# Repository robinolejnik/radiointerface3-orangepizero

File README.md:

# radiointerface3-orangepizero
Interface with audio, ptt, squelch and uart lines to connect 3 radios to an OrangePi Zero

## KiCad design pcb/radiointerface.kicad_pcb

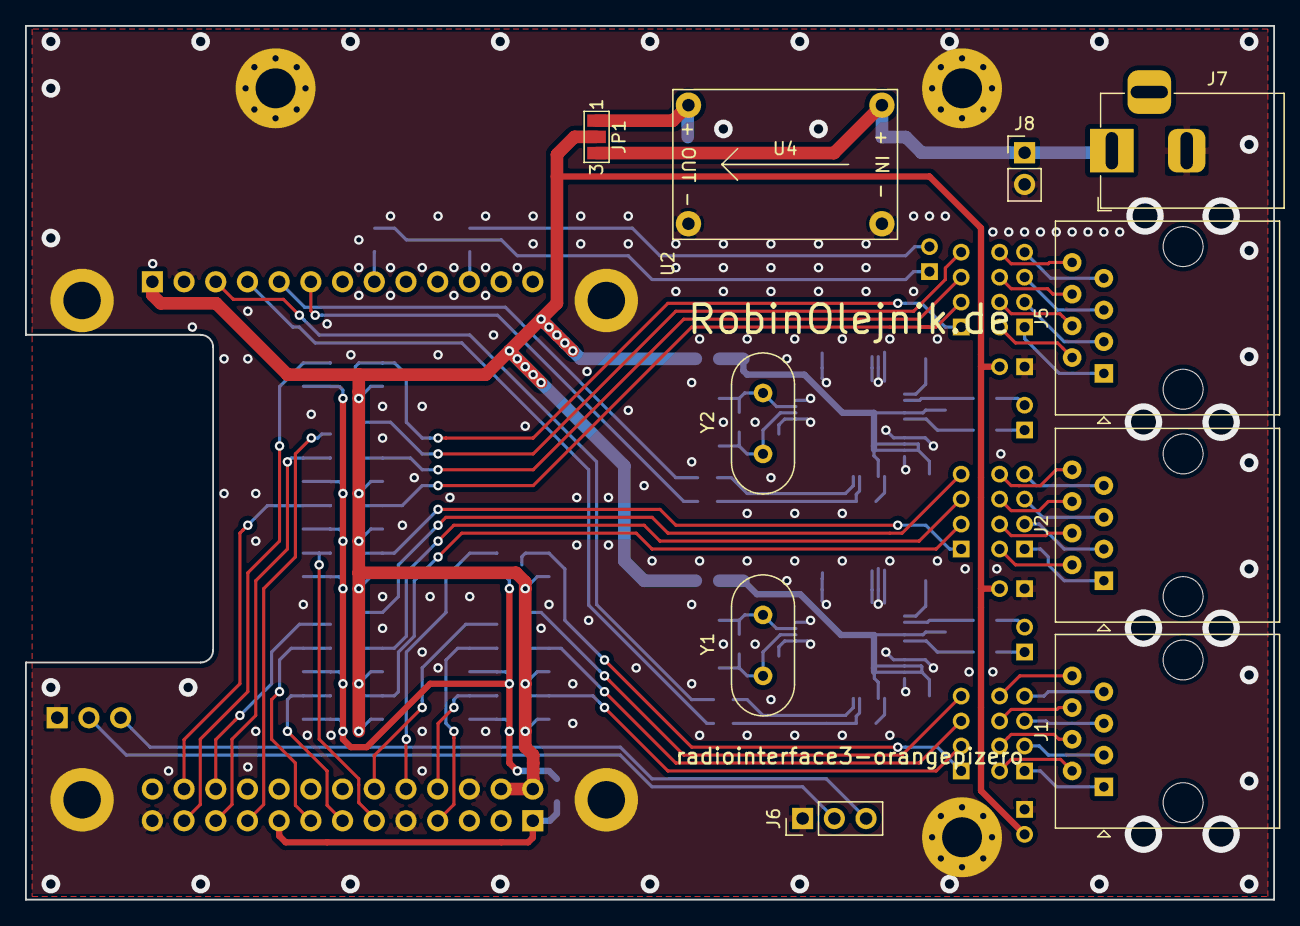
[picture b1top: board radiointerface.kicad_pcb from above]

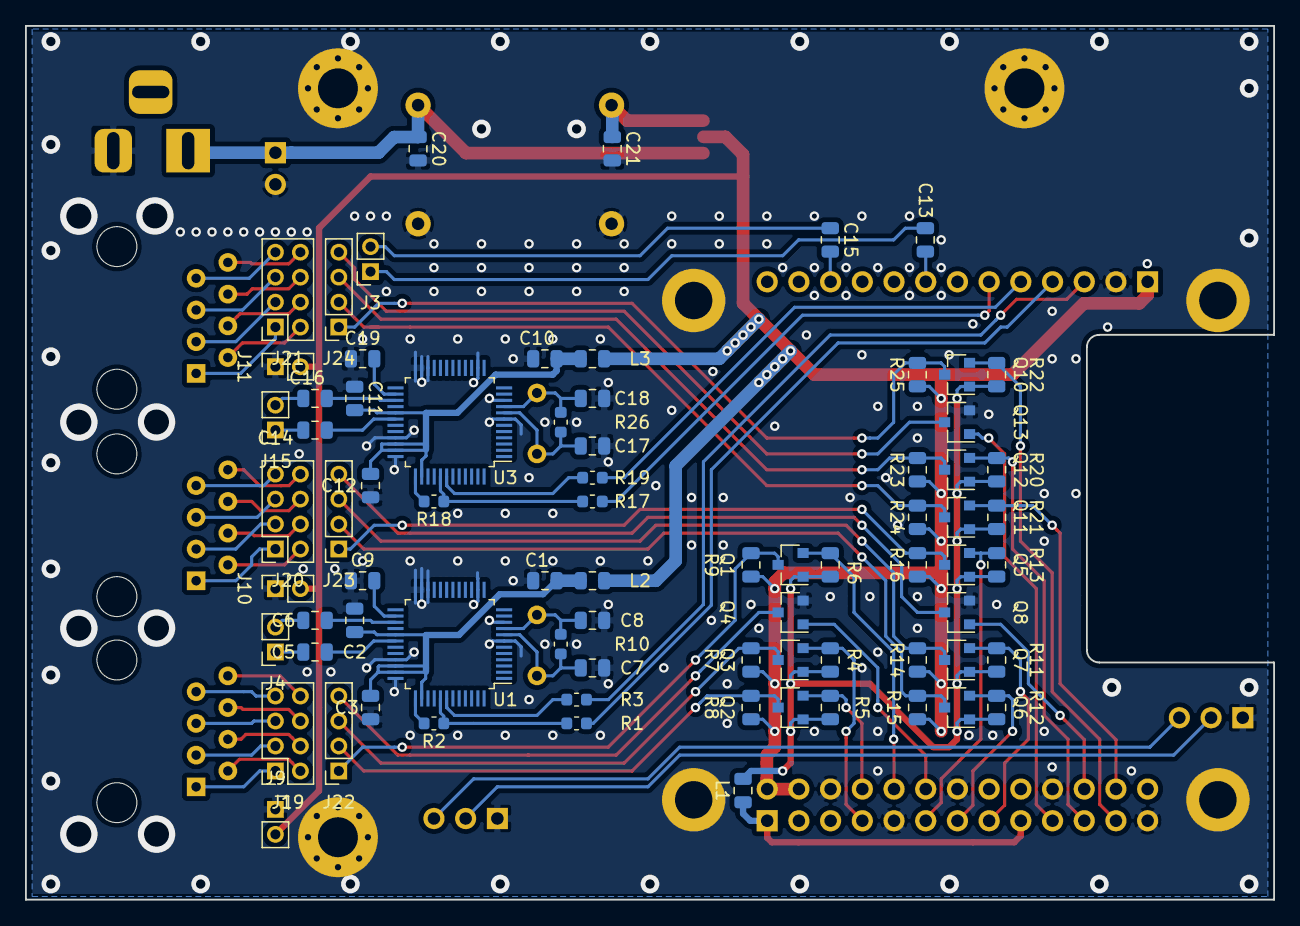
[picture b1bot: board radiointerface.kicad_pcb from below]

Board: 2 copper layers, 100.0 x 70.0 mm, 89 parts (75 on the bottom side), 86 nets.

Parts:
C1, C5, C6, C10, C13, C14, C15, C16: 1u; C_0805_2012Metric
C2, C3, C9, C11, C12, C19: 100n; C_0805_2012Metric
C7, C8, C17, C18: 22p; C_0805_2012Metric
C20, C21: 10u; C_0805_2012Metric
J1, J2, J5: RJ45; RJ45_Amphenol_54602-x08_Horizontal
J3: A3; PinSocket_1x02_P2.00mm_Vertical
J4: A1; PinSocket_1x02_P2.00mm_Vertical
J6: UART; PinHeader_1x03_P2.54mm_Vertical
J7: PWR; BarrelJack_Horizontal
J8: POE; PinHeader_1x02_P2.54mm_Vertical
J9: P1; PinSocket_1x02_P2.00mm_Vertical
J10: P2; PinSocket_1x02_P2.00mm_Vertical
J11: P3; PinSocket_1x02_P2.00mm_Vertical
J15: A2; PinSocket_1x02_P2.00mm_Vertical
J19: R1; PinSocket_2x04_P2.00mm_Vertical
J20: R2; PinSocket_2x04_P2.00mm_Vertical
J21: R3; PinSocket_2x04_P2.00mm_Vertical
J22: S1; PinSocket_1x04_P2.00mm_Vertical
J23: S2; PinSocket_1x04_P2.00mm_Vertical
J24: S3; PinSocket_1x04_P2.00mm_Vertical
JP1: PWR_SEL; SolderJumper-3_P1.3mm_Open_Pad1.0x1.5mm_NumberLabels
L1, L2, L3: 10u; L_0805_2012Metric
MH1, MH2, MH3: M3; MountingHole_3.2mm_M3_Pad_Via
Q1, Q2, Q3, Q4, Q5, Q6, Q7, Q8, Q10, Q11, Q12, Q13: BSS138; SOT-23
R1, R3, R17, R19: 22; R_0603_1608Metric
R2, R18: 1.5k; R_0603_1608Metric
R4, R5, R6, R7, R8, R9, R11, R12, R13, R14, R15, R16, R20, R21, R22, R23, R24, R25: 10k; R_0805_2012Metric
R10, R26: 1M; R_0603_1608Metric
U1, U3: CM108AH; LQFP-48_7x7mm_P0.5mm
U2: OrangePiZero
U4: Mini-360
Y1, Y2: 12M; Crystal_HC49-U_Vertical

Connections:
+3V3: L1.2, Q1.1, Q2.1, Q3.1, Q5.1, Q6.1, Q7.1, Q10.1, Q11.1, Q12.1, R4.1, R5.1, R6.1, R11.1, R12.1, R13.1, R20.1, R21.1, R22.1
+5V: J9.2, J10.2, J11.2, JP1.2, L2.1, L3.1, R7.1, R8.1, R9.1, R14.1, R15.1, R16.1, R23.1, R24.1, R25.1, U2.A02, U2.A04, U2.B01
/RX1_5: J22.1, Q1.3, R9.2
/RX2_5: J23.1, Q5.3, R16.2
/RX3_5: J24.1, Q10.3, R25.2
/SQL1_5: J22.3, Q3.3, R7.2
/SQL2_5: J23.3, Q7.3, R14.2
/SQL3_5: J24.3, Q12.3, R23.2
/TX1_5: J22.2, Q2.3, R8.2
/TX2_5: J23.2, Q6.3, R15.2
/TX3_5: J24.2, Q11.3, R24.2
GND: C1.1, C2.1, C3.1, C7.2, C8.2, C9.1, C10.1, C11.1, C12.1, C17.2, C18.2, C19.1, C20.2, C21.2, J6.1, J7.2, J8.2, J9.1, J10.1, J11.1, MH1.1, MH2.1, MH3.1, Q4.2, Q8.2, Q13.2, U1.7, U1.10, U1.14, U1.22, U1.23, U1.24, U1.33, U1.36, U2.A06, U2.A09, U2.A14, U2.A20, U2.A25, U2.B02, U2.C1, U2.D1, U2.D2, U2.D3, U2.D4, U3.7, U3.10, U3.14, U3.22, U3.23, U3.24, U3.33, U3.36, U4.2, U4.4
unnamed: C1.2, C2.2, C3.2, L2.2, U1.29, U1.34, U1.35, U1.38
unnamed: C5.1, J4.1
unnamed: C5.2, U1.30
unnamed: C6.1, J4.2
unnamed: C6.2, U1.27
unnamed: C7.1, R10.2, U1.8, Y1.1
unnamed: C8.1, R10.1, U1.9, Y1.2
unnamed: C9.2, U1.26
unnamed: C10.2, C11.2, C12.2, L3.2, U3.29, U3.34, U3.35, U3.38
unnamed: C13.1, J3.1
unnamed: C13.2, U2.B08
unnamed: C14.1, J15.1
unnamed: C14.2, U3.30
unnamed: C15.1, J3.2
unnamed: C15.2, U2.B11
unnamed: C16.1, J15.2
unnamed: C16.2, U3.27
unnamed: C17.1, R26.2, U3.8, Y2.1
unnamed: C18.1, R26.1, U3.9, Y2.2
unnamed: C19.2, U3.26
unnamed: C20.1, J7.1, J8.1, JP1.3, U4.1
unnamed: C21.1, JP1.1, U4.3
unnamed: J1.1, J19.1
unnamed: J1.2, J19.2
unnamed: J1.3, J19.3
unnamed: J1.4, J19.4
unnamed: J1.5, J19.5
unnamed: J1.6, J19.6
unnamed: J1.7, J19.7
unnamed: J1.8, J19.8
unnamed: J2.1, J20.1
unnamed: J2.2, J20.2
unnamed: J2.3, J20.3
unnamed: J2.4, J20.4
unnamed: J2.5, J20.5
unnamed: J2.6, J20.6
unnamed: J2.7, J20.7
unnamed: J2.8, J20.8
unnamed: J6.2, U2.C2
unnamed: J6.3, U2.C3
unnamed: J5.1, J21.1
unnamed: J5.2, J21.2
unnamed: J5.3, J21.3
unnamed: J5.4, J21.4
unnamed: J5.5, J21.5
unnamed: J5.6, J21.6
unnamed: J5.7, J21.7
unnamed: J5.8, J21.8
unnamed: J22.4, Q4.3
unnamed: J23.4, Q8.3
unnamed: J24.4, Q13.3
unnamed: L1.1, U2.A01, U2.A17
unnamed: R1.1, R2.1, U1.41
unnamed: R2.2, U1.37
unnamed: R3.1, U1.42
unnamed: R17.1, R18.1, U3.41
unnamed: R18.2, U3.37
unnamed: R19.1, U3.42
PTT1: Q4.1, U2.A12
PTT2: Q8.1, U2.A22
PTT3: Q13.1, U2.A19
RX1: Q1.2, R6.2, U2.A10
RX2: Q5.2, R13.2, U2.A11
RX3: Q10.2, R22.2, U2.A23
SQL1: Q3.2, R4.2, U2.A07
SQL2: Q7.2, R11.2, U2.A15
SQL3: Q12.2, R20.2, U2.A21
TX1: Q2.2, R5.2, U2.A08
TX2: Q6.2, R12.2, U2.A13
TX3: Q11.2, R21.2, U2.A24
USB1M: R3.2, U2.B03
USB1P: R1.2, U2.B04
USB2M: R19.2, U2.B05
USB2P: R17.2, U2.B06

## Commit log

2020-04-04 Added the PCB KiCad project.
2020-04-04 Added the frontpanel KiCad project.
